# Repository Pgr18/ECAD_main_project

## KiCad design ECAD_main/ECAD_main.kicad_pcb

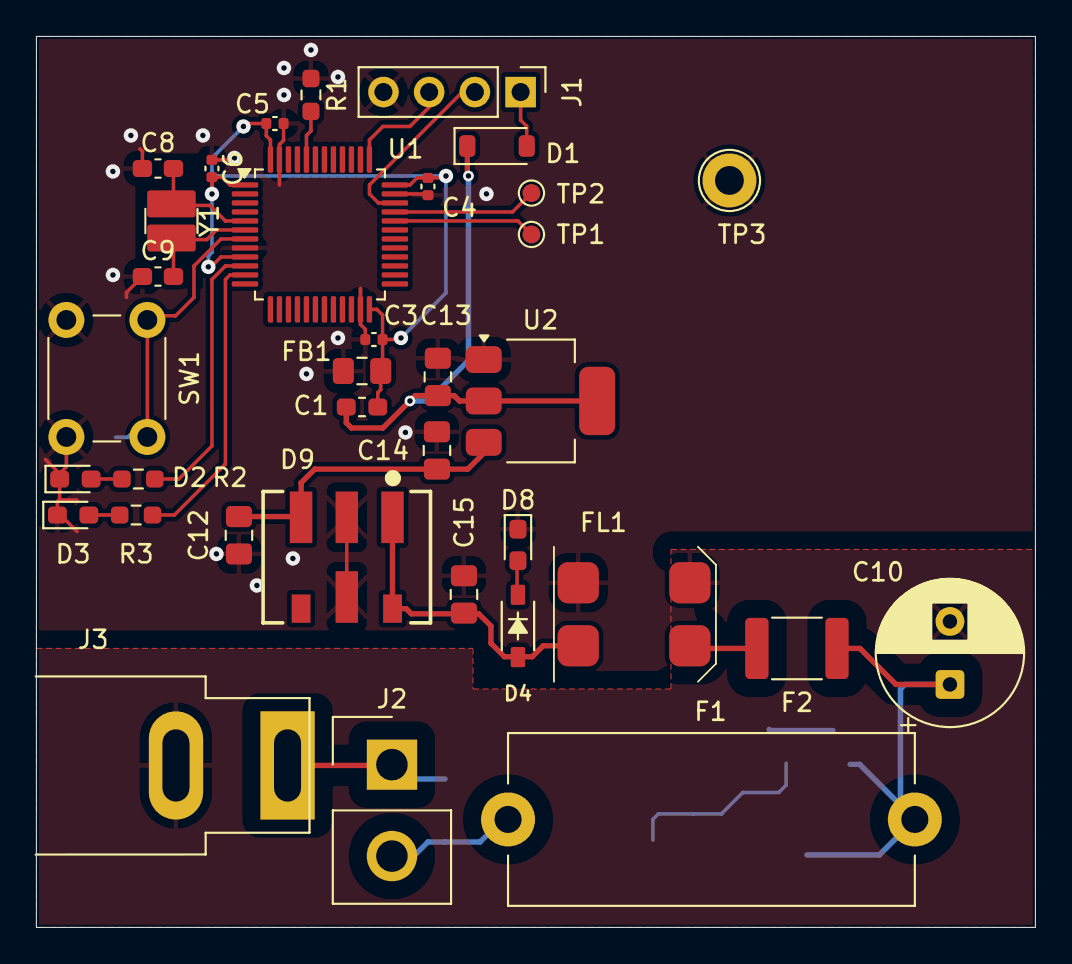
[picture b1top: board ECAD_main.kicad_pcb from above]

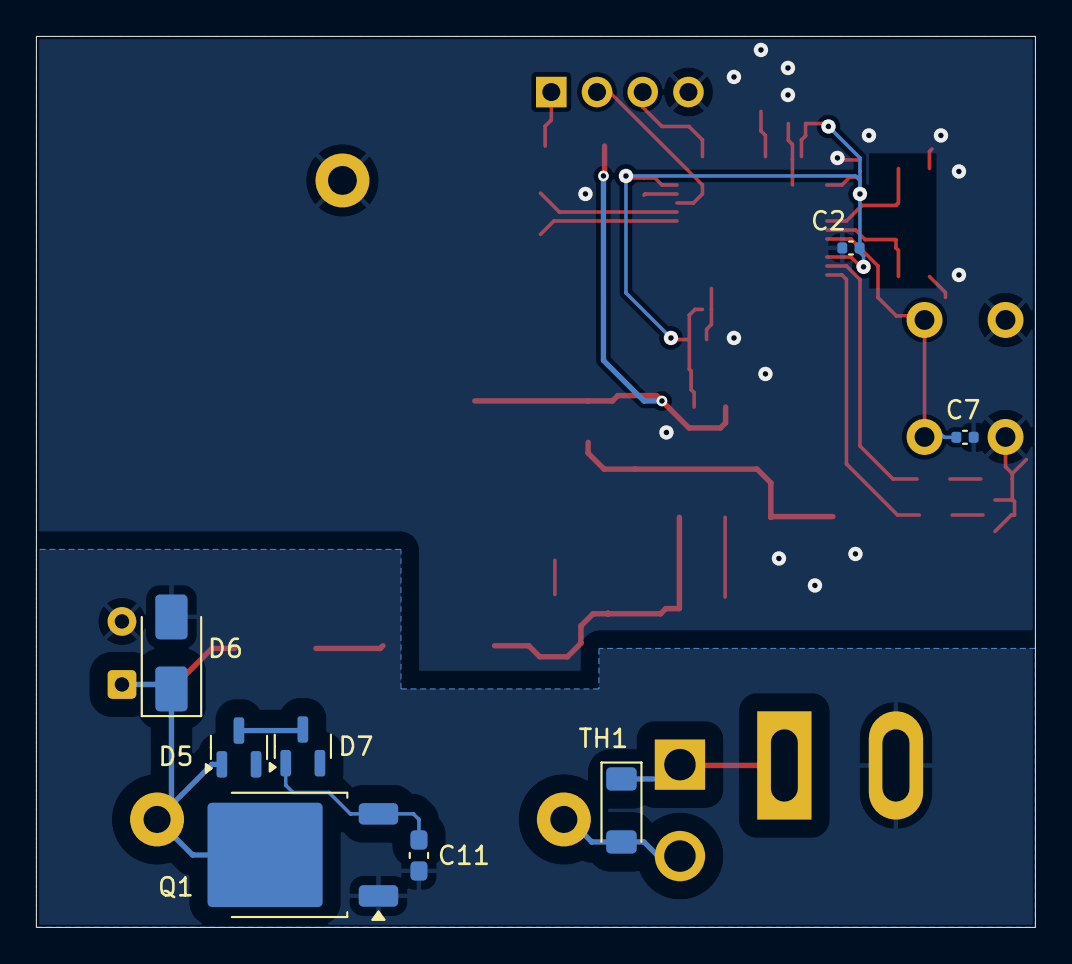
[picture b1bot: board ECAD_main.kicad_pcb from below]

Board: 4 copper layers, 55.5 x 49.5 mm, 44 parts (8 on the bottom side), 26 nets.

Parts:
C1: 4.7u/6.3V; C_0805_2012Metric_Pad1.18x1.45mm_HandSolder
C2, C3, C4, C5, C6, C7: 100n/6.3V; C_0402_1005Metric
C8, C9: 8p/50V; C_0603_1608Metric_Pad1.08x0.95mm_HandSolder
C10: 100uF/50V; CP_Radial_D8.0mm_P3.50mm
C11: 100n/50V; C_0603_1608Metric_Pad1.08x0.95mm_HandSolder
C12, C15: 22uF/25V; C_0805_2012Metric_Pad1.18x1.45mm_HandSolder
C13: 2.2uF/10V; C_0805_2012Metric_Pad1.18x1.45mm_HandSolder
C14: 2.2uF/50V; C_0805_2012Metric_Pad1.18x1.45mm_HandSolder
D1: BAT43W; D_SOD-123
D2, D8: FYLS-0603UGC; LED_0603_1608Metric_Pad1.05x0.95mm_HandSolder
D3: FYLS-0603URC; LED_0603_1608Metric_Pad1.05x0.95mm_HandSolder
D4: NSI45020T1G; SOD3716X135N
D5, D7: BZX84C13; SOT-23
D6: SMAJ13CA; D_SMA
D9: K7805MT-500R4; K78xxMT-500R4
F1: Fuse; Fuseholder_Cylinder-5x20mm_Stelvio-Kontek_PTF78_Horizontal_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
F2: FSMD050-30-R; Fuse_1812_4532Metric_Pad1.30x3.40mm_HandSolder
FB1: BLM18PG330SN1D; L_0603_1608Metric_Pad1.05x0.95mm_HandSolder
FL1: CPFC805NP-100M05; CPFC805
HU1: OZON_TECH_LOGO
J1: DEBUG_01x04; PinHeader_1x04_P2.54mm_Vertical
J2: TO_SWITCH; Samtec_HPM-02-01-x-S_Straight_1x02_Pitch5.08mm
J3: DS-201; DS201b
Q1: BT137S-600; TO-252-2
R1: 100k; R_0603_1608Metric_Pad0.98x0.95mm_HandSolder
R2, R3: 680; R_0603_1608Metric_Pad0.98x0.95mm_HandSolder
SW1: KLS7-TS6606-13.0; SW_PUSH_6mm_H4.3mm
TH1: PMLL4148L; D_MiniMELF
TP1, TP2: TestPoint_Pad_D1.0mm
TP3: GNDPWR; TestPoint_Loop_D2.60mm_Drill1.6mm_Beaded
U1: STM32F103C8T6; LQFP-48_7x7mm_P0.5mm
U2: AMS1117-3.3; SOT-223-3_TabPin2
Y1: NX3225GD-8MHz; NX3225GD

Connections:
3V3: C13.1, D1.1 (K), FB1.1, U2.2 (VO)
/LED_SMALL_ERROR: R3.2, U1.11 (PA1)
/LED_SMALL_OK: R2.2, U1.10 (PA0)
/MCU_SMALL_VDD: C1.1, C2.2, C3.2, C4.2, C5.2, C6.2, FB1.2, U1.1 (VBAT), U1.9 (VDDA), U1.24 (VDD), U1.36 (VDD), U1.48 (VDD)
/SWCLK_SMALL: J1.3, U1.37 (PA14)
/SWDIO_SMALL: J1.2, U1.34 (PA13)
/USB_DM_SMALL: TP1.1, U1.32 (PA11)
/USB_DP_SMALL: TP2.1, U1.33 (PA12)
/power/+12V_POWER: C15.1, D4.2, D9.1 (+Vin), D9.6 (Ctrl), FL1.2
/power/PWR_BUT: J2.1, J3.1, TH1.1 (K)
/power/PWR_In: F1.1, J2.2, TH1.2 (A)
/power/PWR_prot: C10.1, D5.1 (A), D6.1 (A1), F1.2, F2.1, Q1.2 (A2)
/power/Pow1: F2.2, FL1.1
DGND: C1.2, C2.1, C3.1, C4.1, C5.1, C6.1, C7.1, C8.1, C9.1, C12.2, C13.2, C14.2, C15.2, D2.1 (K), D3.1 (K), D8.1 (K), D9.2 (GND), D9.5 (GND), FL1.4, J1.4, R1.1, SW1.1, TP3.1, U1.8 (VSSA), U1.23 (VSS), U1.35 (VSS), U1.47 (VSS), U2.1 (GND)
GNDPWR_IN: C10.2, C11.2, D6.2 (A2), FL1.3, J3.2, Q1.1 (A1)
unnamed: D1.2 (A), J1.1
unnamed: D2.2 (A), R2.1
unnamed: D3.2 (A), R3.1
unnamed: D5.3 (K), D7.3 (K)
unnamed: C11.1, D7.1 (A), Q1.3 (G)
unnamed: D4.1, D8.2 (A)
unnamed: C12.1, C14.1, D9.3 (+Vo), U2.3 (VI)
unnamed: R1.2, U1.44 (BOOT0)
unnamed: C7.2, SW1.2, U1.7 (NRST)
unnamed: C8.2, U1.5 (PD0), Y1.2
unnamed: C9.2, U1.6 (PD1), Y1.1

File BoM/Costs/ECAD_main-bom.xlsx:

|  | KiBot Bill of Materials
 |  | Schematic: | ECAD_main | Component Groups: | 31
 |  | Variant: | default | Component Count: | 41 (34 SMD/ 6 THT)
 |  | Revision: |  | Fitted Components: | 41 (34 SMD/ 6 THT)
 |  | Date: | 2025-10-27_20-20-09 | Number of PCBs: | 1
 |  | KiCad Version: | 9.0.1+1 | Total Components: | 41
Row | Description | Part | References | Value | Footprint | Quantity Per PCB | Status | Datasheet | Quantity | Sim.Library | Sim.Name | Sim.Params | Sim.Device | Sim.Pins | MF | SNAPEDA_PACKAGE_ID | Package | Price | Check_prices | STANDARD | PARTREV | SnapEDA_Link | MP | Description_1 | Availability | MANUFACTURER
1 |  | C | C11 | 100n/50V | C_0603_1608Metric_Pad1.08x0.95mm_HandSolder | 1 |  | ~
2 |  | C | C2 C3 C4 C5 C6 C7 | 100n/6.3V | C_0402_1005Metric | 6 |  | ~
3 |  | C_Polarized | C10 | 100uF/50V | CP_Radial_D8.0mm_P3.50mm | 1 |  | ~
4 |  | C | C13 | 2.2uF/10V | C_0805_2012Metric_Pad1.18x1.45mm_HandSolder | 1 |  | ~
5 |  | C | C14 | 2.2uF/50V | C_0805_2012Metric_Pad1.18x1.45mm_HandSolder | 1 |  | ~
6 |  | C | C12 C15 | 22uF/25V | C_0805_2012Metric_Pad1.18x1.45mm_HandSolder | 2 |  | ~
7 |  | C | C1 | 4.7u/6.3V | C_0805_2012Metric_Pad1.18x1.45mm_HandSolder | 1 |  | ~
8 |  | C | C8 C9 | 8p/50V | C_0603_1608Metric_Pad1.08x0.95mm_HandSolder | 2 |  | ~
9 |  | D_Schottky | D1 | BAT43W | D_SOD-123 | 1 |  | ~
10 |  | BZX84Cxx | D5 D7 | BZX84C13 | SOT-23 | 2 |  | https://diotec.com/tl_files/diotec/files/pdf/datasheets/bzx8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
11 |  | LED | D2 D8 | FYLS-0603UGC | LED_0603_1608Metric_Pad1.05x0.95mm_HandSolder | 2 |  | ~ |  |  |  |  |  | 1=K 2=A
12 |  | LED | D3 | FYLS-0603URC | LED_0603_1608Metric_Pad1.05x0.95mm_HandSolder | 1 |  | ~ |  |  |  |  |  | 1=K 2=A
13 |  | K78xxMT-500R4 | D9 | K7805MT-500R4 | K78xxMT-500R4 | 1
14 |  | NSI45020T1G | D4 | NSI45020T1G | SOD3716X135N | 1 |  |  |  |  |  |  |  |  | ON Semiconductor | 5492 | SOD-123-2 ON Semiconductor | None | https://www.snapeda.com/parts/NSI45020T1G/Onsemi/view-part/?ref=eda | IPC-7351B | 6 | https://www.snapeda.com/parts/NSI45020T1G/Onsemi/view-part/?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 | NSI45020T1G | Current Regulator Regulator High/Low-Side 20mA SOD-123 | In Stock
15 |  | SMAJ24A | D6 | SMAJ13CA | D_SMA | 1 |  | https://www.littelfuse.com/media?resourcetype=datasheets&ite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
16 |  | Polyfuse | F2 | FSMD050-30-R | Fuse_1812_4532Metric_Pad1.30x3.40mm_HandSolder | 1 |  | ~
17 |  | Fuse | F1 | Fuse | Fuseholder_Cylinder-5x20mm_Stelvio-Kontek_PTF78_Horizontal_Open | 1 |  | ~
18 |  | FerriteBead_Small | FB1 | BLM18PG330SN1D | L_0603_1608Metric_Pad1.05x0.95mm_HandSolder | 1 |  | ~
19 |  | Filter_EMI_CommonMode | FL1 | CPFC805NP-100M05 | CPFC805 | 1 |  | ~
20 |  | LOGO | HU1 | ~ | OZON_TECH_LOGO | 1
21 |  | Conn_01x04 | J1 | DEBUG_01x04 | PinHeader_1x04_P2.54mm_Vertical | 1 |  | ~
22 |  | Jack-DC | J3 | DS-201 | DS201b | 1 |  | ~
23 |  | Conn_01x02 | J2 | TO_SWITCH | Samtec_HPM-02-01-x-S_Straight_1x02_Pitch5.08mm | 1 |  | ~
24 |  | BT138-600 | Q1 | BT137S-600 | TO-252-2 | 1 |  | https://assets.nexperia.com/documents/data-sheet/BT138_SER_D_E.pdf
25 |  | R | R2 R3 | 680 | R_0603_1608Metric_Pad0.98x0.95mm_HandSolder | 2 |  | ~
26 |  | R | R1 | 100k | R_0603_1608Metric_Pad0.98x0.95mm_HandSolder | 1 |  | ~
27 |  | SW_Push | SW1 | KLS7-TS6606-13.0 | SW_PUSH_6mm_H4.3mm | 1 |  | ~
28 |  | KTY85 | TH1 | PMLL4148L | D_MiniMELF | 1 |  | http://www.nxp.com/documents/other/SC17_GENERAL_TEMP_1996_3.pdf
29 |  | AMS1117-3.3 | U2 | AMS1117-3.3 | SOT-223-3_TabPin2 | 1 |  | http://www.advanced-monolithic.com/pdf/ds1117.pdf
30 |  | STM32F103C8Tx | U1 | STM32F103C8T6 | LQFP-48_7x7mm_P0.5mm | 1 |  | https://www.st.com/resource/en/datasheet/stm32f103c8.pdf
31 |  | Crystal | Y1 | NX3225GD-8MHz | NX3225GD | 1 |  | ~

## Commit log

2025-09-11 Added libraries submodule
2025-09-11 Создали проект, добавили библиотеки
2025-10-27 Rename test.yml to kibot_quick_start.yml
2025-10-27 fixed
2025-10-27 Deploying to main from @ Pgr18/ECAD_main_project@fa77bc7d525d1915cc1f8815ceef3057f2a52317 🚀
2025-10-29 Revert "Update kibot_quick_start.yml"
    This reverts commit fa77bc7d525d1915cc1f8815ceef3057f2a52317.
2025-10-29 Revert "Update kibot_quick_start.yml"
    This reverts commit debe348333feb3c2b229896053e82845d2973919.
